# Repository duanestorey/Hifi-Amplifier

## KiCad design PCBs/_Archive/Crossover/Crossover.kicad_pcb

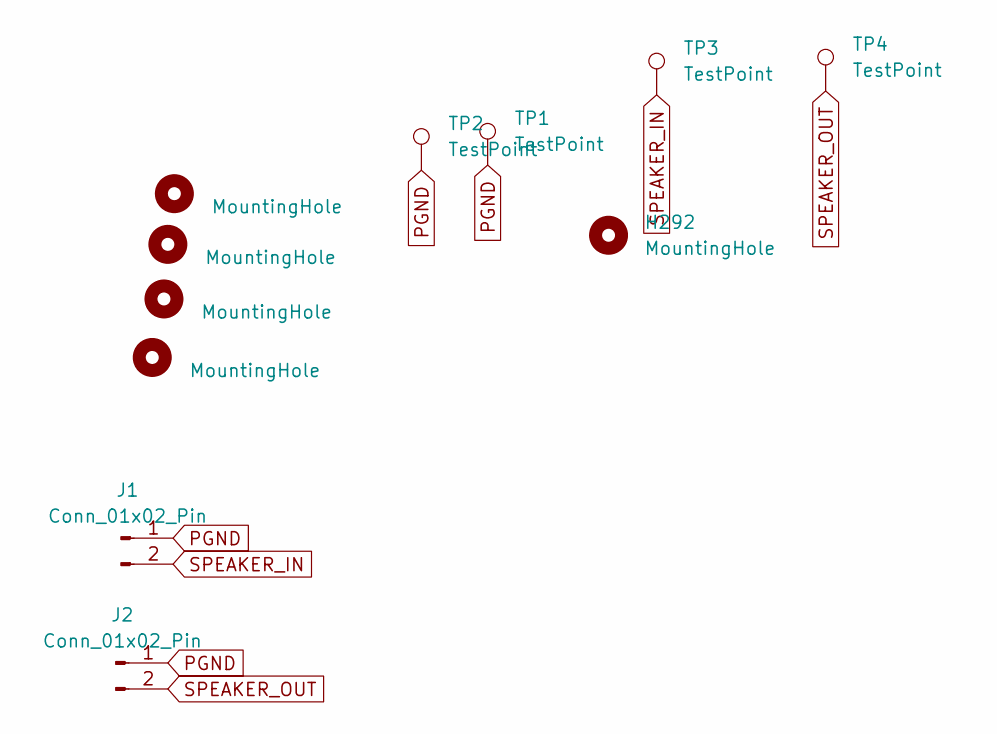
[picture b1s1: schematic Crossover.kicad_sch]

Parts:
H1, H2, H3, H4: MountingHole; MountingHole_3.2mm_M3
H292: MountingHole; MountingHole_2.2mm_M2
J1, J2: Conn_01x02_Pin; JST_VH_B2P-VH_1x02_P3.96mm_Vertical
TP1, TP2, TP3, TP4: TestPoint; TestPoint_Loop_D2.50mm_Drill1.85mm

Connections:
PGND: J1.1, J2.1, TP1.1, TP2.1
SPEAKER_IN: J1.2, TP3.1
SPEAKER_OUT: J2.2, TP4.1

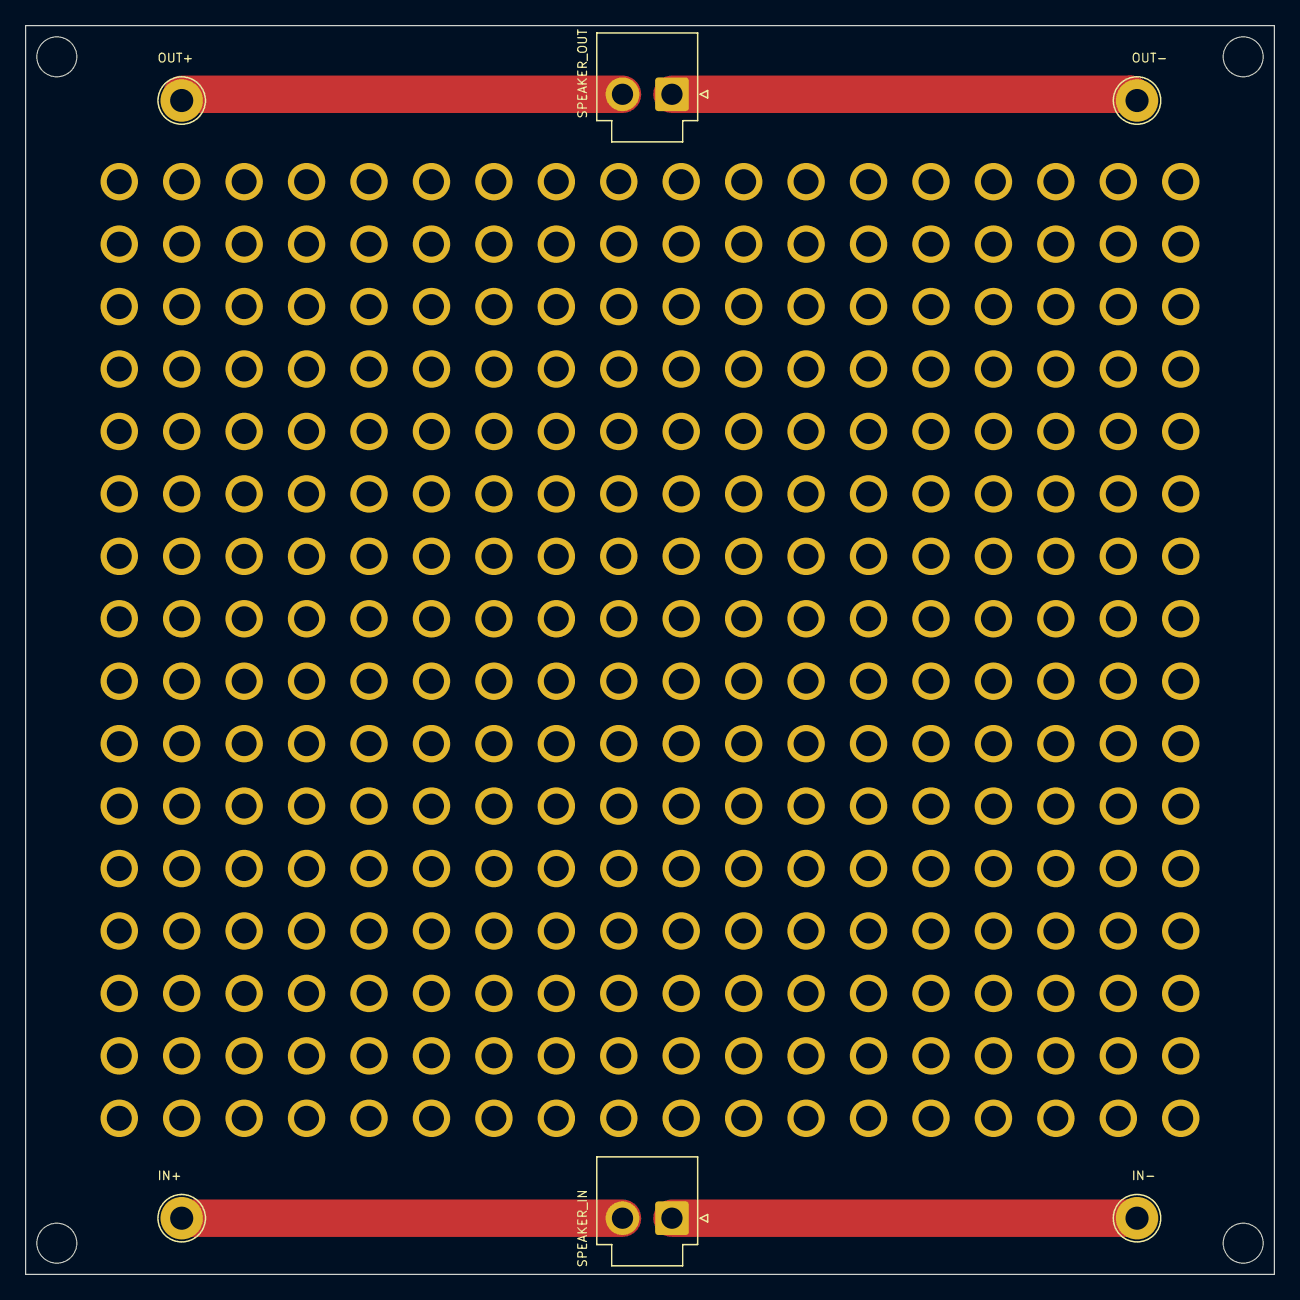
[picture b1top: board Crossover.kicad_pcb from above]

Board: 2 copper layers, 100.0 x 100.0 mm, 298 parts (0 on the bottom side), 3 nets.

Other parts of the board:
H5, H6, H7, H8, H9, H10, H11, H12, H13, H14, H15, H16, H17, H18, H19, H20, H21, H22, H23, H24, H25, H26, H27, H28, H29, H30, H31, H32, H33, H34, H35, H36, H37, H38, H39, H40, H41, H42, H43, H44, H45, H46, H47, H48, H49, H50, H51, H52, H53, H54, H55, H56, H57, H58, H59, H60, H61, H62, H63, H64, H65, H66, H67, H68, H69, H70, H71, H72, H73, H74, H75, H76, H77, H78, H79, H80, H81, H82, H83, H84, H85, H86, H87, H88, H89, H90, H91, H92, H93, H94, H95, H96, H97, H98, H99, H100, H101, H102, H103, H104, H105, H106, H107, H108, H109, H110, H111, H112, H113, H114, H115, H116, H117, H118, H119, H120, H121, H122, H123, H124, H125, H126, H127, H128, H129, H130, H131, H132, H133, H134, H135, H136, H137, H138, H139, H140, H141, H142, H143, H144, H145, H146, H147, H148, H149, H150, H151, H152, H153, H154, H155, H156, H157, H158, H159, H160, H161, H162, H163, H164, H165, H166, H167, H168, H169, H170, H171, H172, H173, H174, H175, H176, H177, H178, H179, H180, H181, H182, H183, H184, H185, H186, H187, H188, H189, H190, H191, H192, H193, H194, H195, H196, H197, H198, H199, H200, H201, H202, H203, H204, H205, H206, H207, H208, H209, H210, H211, H212, H213, H214, H215, H216, H217, H218, H219, H220, H221, H222, H223, H224, H225, H226, H227, H228, H229, H230, H231, H232, H233, H234, H235, H236, H237, H238, H239, H240, H241, H242, H243, H244, H245, H246, H247, H248, H249, H250, H251, H252, H253, H254, H255, H256, H257, H258, H259, H260, H261, H262, H263, H264, H265, H266, H267, H268, H269, H270, H271, H272, H273, H274, H275, H276, H277, H278, H279, H280, H281, H282, H283, H284, H285, H286, H287, H288, H289, H290, H291: MountingHole; MountingHole_2.2mm_M2

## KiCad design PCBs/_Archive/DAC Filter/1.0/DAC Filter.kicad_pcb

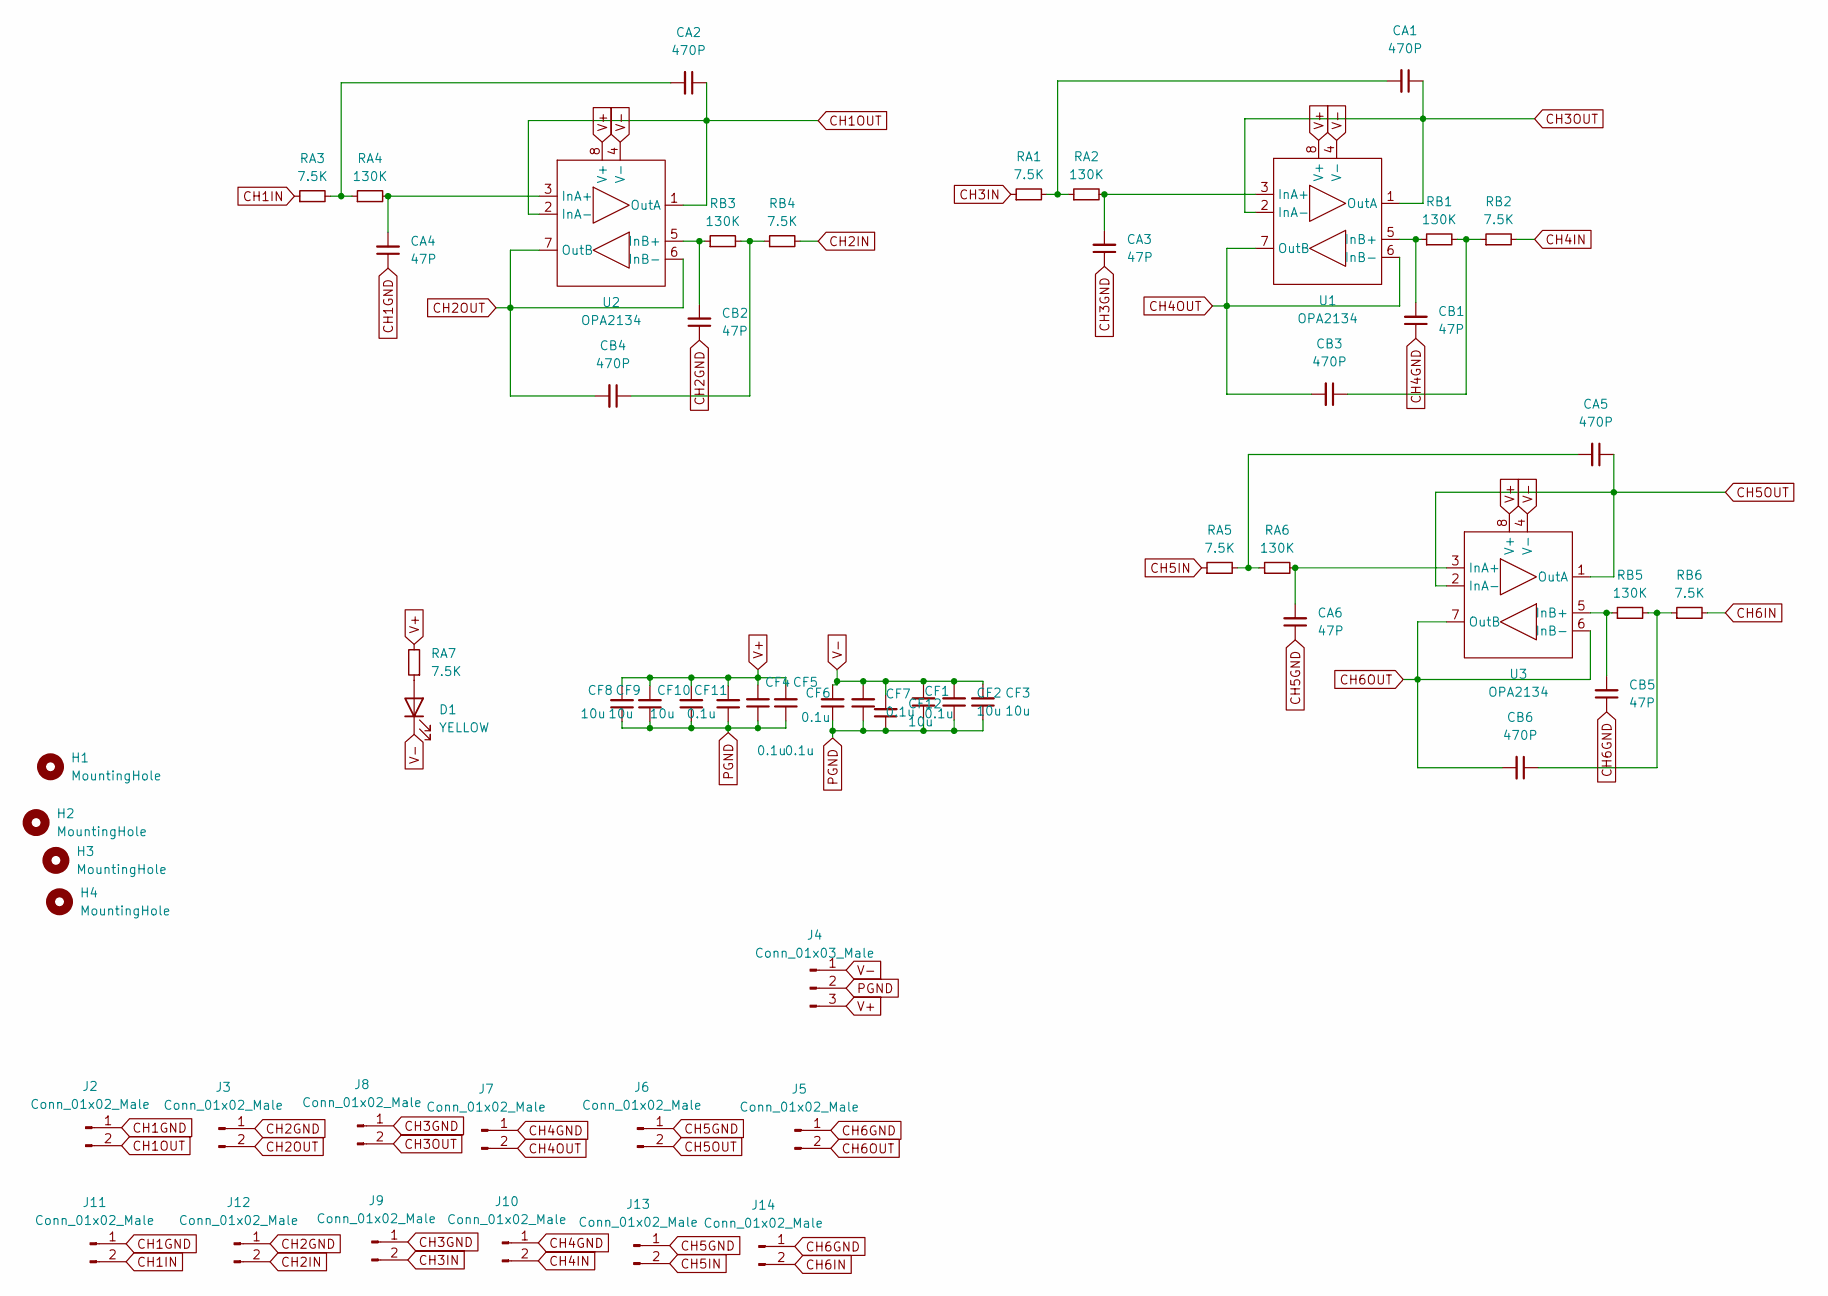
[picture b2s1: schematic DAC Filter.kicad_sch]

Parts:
CA1, CA2, CA5: 470P; C_1206_3216Metric_Pad1.33x1.80mm_HandSolder
CA3, CA4, CA6: 47P; C_1206_3216Metric_Pad1.33x1.80mm_HandSolder
CB1, CB2, CB5: 47P; C_1206_3216Metric_Pad1.33x1.80mm_HandSolder
CB3, CB4, CB6: 470P; C_1206_3216Metric_Pad1.33x1.80mm_HandSolder
CF1, CF4, CF5, CF6, CF7, CF11: 0.1u; C_0805_2012Metric_Pad1.18x1.45mm_HandSolder
CF2, CF3, CF8, CF9, CF10, CF12: 10u; C_1206_3216Metric_Pad1.33x1.80mm_HandSolder
D1: YELLOW; LED_0805_2012Metric_Pad1.15x1.40mm_HandSolder
H1, H2, H3, H4: MountingHole; MountingHole_3.2mm_M3
J2, J3, J5, J6, J7, J8, J9, J10, J11, J12, J13, J14: Conn_01x02_Male; JST_PH_B2B-PH-K_1x02_P2.00mm_Vertical
J4: Conn_01x03_Male; JST_PH_B3B-PH-K_1x03_P2.00mm_Vertical
RA1, RA3, RA5: 7.5K; R_1206_3216Metric_Pad1.30x1.75mm_HandSolder
RA2, RA4, RA6: 130K; R_1206_3216Metric_Pad1.30x1.75mm_HandSolder
RA7: 7.5K; R_0603_1608Metric
RB1, RB3, RB5: 130K; R_1206_3216Metric_Pad1.30x1.75mm_HandSolder
RB2, RB4, RB6: 7.5K; R_1206_3216Metric_Pad1.30x1.75mm_HandSolder
U1, U2, U3: OPA2134; DIP-8_W7.62mm_Socket

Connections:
CH1GND: CA4.1, J2.1, J11.1
CH1IN: J11.2, RA3.1
CH1OUT: CA2.1, J2.2, U2.1 (OutA), U2.2 (InA-)
CH2GND: CB2.1, J3.1, J12.1
CH2IN: J12.2, RB4.2
CH2OUT: CB4.2, J3.2, U2.6 (InB-), U2.7 (OutB)
CH3GND: CA3.1, J8.1, J9.1
CH3IN: J9.2, RA1.1
CH3OUT: CA1.1, J8.2, U1.1 (OutA), U1.2 (InA-)
CH4GND: CB1.1, J7.1, J10.1
CH4IN: J10.2, RB2.2
CH4OUT: CB3.2, J7.2, U1.6 (InB-), U1.7 (OutB)
CH5GND: CA6.1, J6.1, J13.1
CH5IN: J13.2, RA5.1
CH5OUT: CA5.1, J6.2, U3.1 (OutA), U3.2 (InA-)
CH6GND: CB5.1, J5.1, J14.1
CH6IN: J14.2, RB6.2
CH6OUT: CB6.2, J5.2, U3.6 (InB-), U3.7 (OutB)
unnamed: CA1.2, RA1.2, RA2.1
unnamed: CA2.2, RA3.2, RA4.1
unnamed: CA5.2, RA5.2, RA6.1
unnamed: CB3.1, RB1.2, RB2.1
unnamed: CB4.1, RB3.2, RB4.1
unnamed: CB6.1, RB5.2, RB6.1
unnamed: D1.2 (A), RA7.1
unnamed: CA3.2, RA2.2, U1.3 (InA+)
unnamed: CB1.2, RB1.1, U1.5 (InB+)
unnamed: CA4.2, RA4.2, U2.3 (InA+)
unnamed: CB2.2, RB3.1, U2.5 (InB+)
unnamed: CA6.2, RA6.2, U3.3 (InA+)
unnamed: CB5.2, RB5.1, U3.5 (InB+)
PGND: CF1.1, CF2.1, CF3.1, CF4.1, CF5.1, CF6.1, CF7.1, CF8.1, CF9.1, CF10.1, CF11.1, CF12.1, J4.2
V+: CF4.2, CF5.2, CF8.2, CF9.2, CF10.2, CF11.2, J4.3, RA7.2, U1.8 (V+), U2.8 (V+), U3.8 (V+)
V-: CF1.2, CF2.2, CF3.2, CF6.2, CF7.2, CF12.2, D1.1 (K), J4.1, U1.4 (V-), U2.4 (V-), U3.4 (V-)

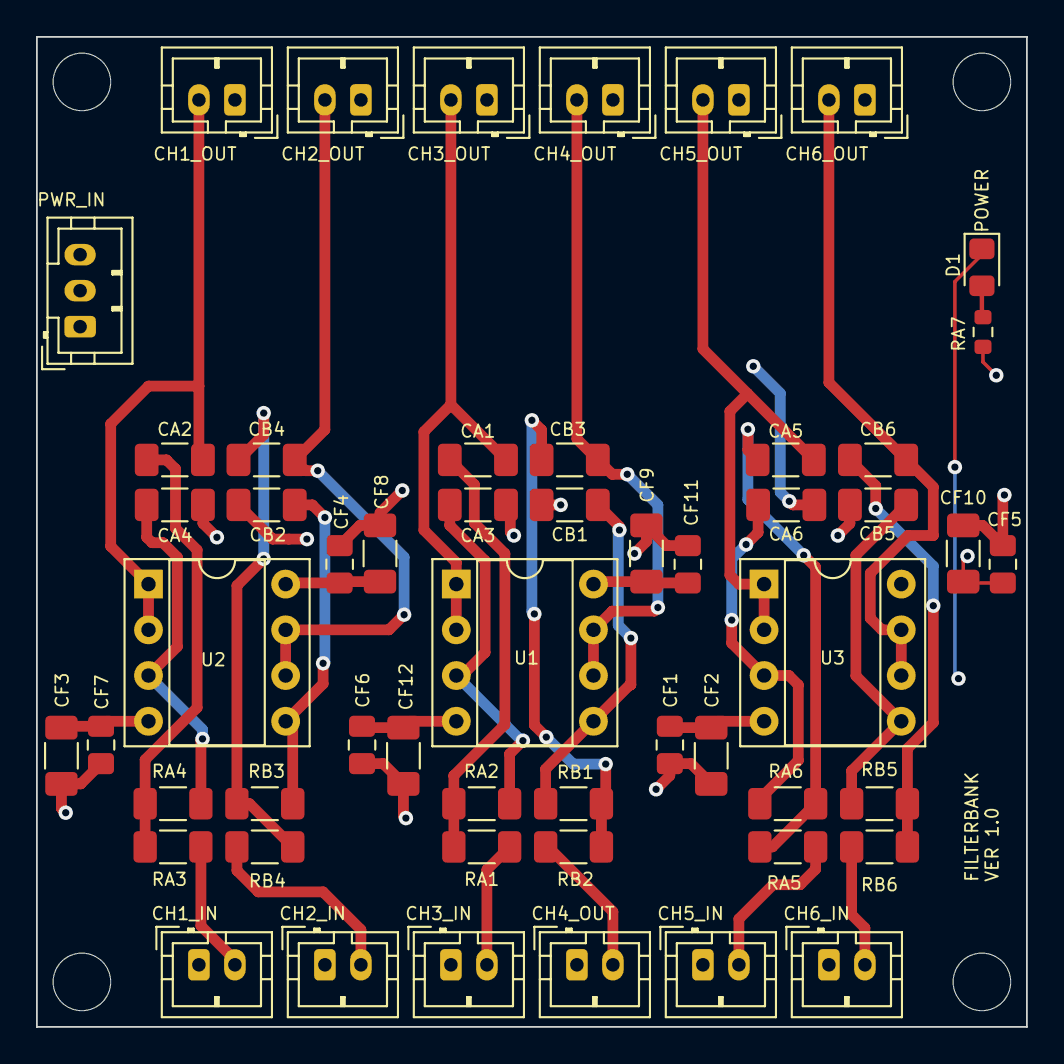
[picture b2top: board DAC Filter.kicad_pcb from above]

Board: 4 copper layers, 55.0 x 55.0 mm, 58 parts (0 on the bottom side), 34 nets.

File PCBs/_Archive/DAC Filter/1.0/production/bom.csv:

Designator,Footprint,Quantity,Value,LCSC Part #
"CA1, CA2, CA5, CB3, CB4, CB6",C_1206_3216Metric_Pad1.33x1.80mm_HandSolder,6,470P,
"CA3, CA4, CA6, CB1, CB2, CB5",C_1206_3216Metric_Pad1.33x1.80mm_HandSolder,6,47P,
"CF1, CF11, CF4, CF5, CF6, CF7",C_0805_2012Metric_Pad1.18x1.45mm_HandSolder,6,0.1u,
"CF10, CF12, CF2, CF3, CF8, CF9",C_1206_3216Metric_Pad1.33x1.80mm_HandSolder,6,10u,
D1,LED_0805_2012Metric_Pad1.15x1.40mm_HandSolder,1,YELLOW,
"H1, H2, H3, H4",MountingHole_3.2mm_M3,4,MountingHole,
"J10, J11, J12, J13, J14, J2, J3, J5, J6, J7, J8, J9",JST_PH_B2B-PH-K_1x02_P2.00mm_Vertical,12,Conn_01x02_Male,
J4,JST_PH_B3B-PH-K_1x03_P2.00mm_Vertical,1,Conn_01x03_Male,
"RA1, RA3, RA5, RB2, RB4, RB6",R_1206_3216Metric_Pad1.30x1.75mm_HandSolder,6,7.5K,
"RA2, RA4, RA6, RB1, RB3, RB5",R_1206_3216Metric_Pad1.30x1.75mm_HandSolder,6,130K,
RA7,R_0603_1608Metric,1,7.5K,
"U1, U2, U3",DIP-8_W7.62mm_Socket,3,OPA2134,

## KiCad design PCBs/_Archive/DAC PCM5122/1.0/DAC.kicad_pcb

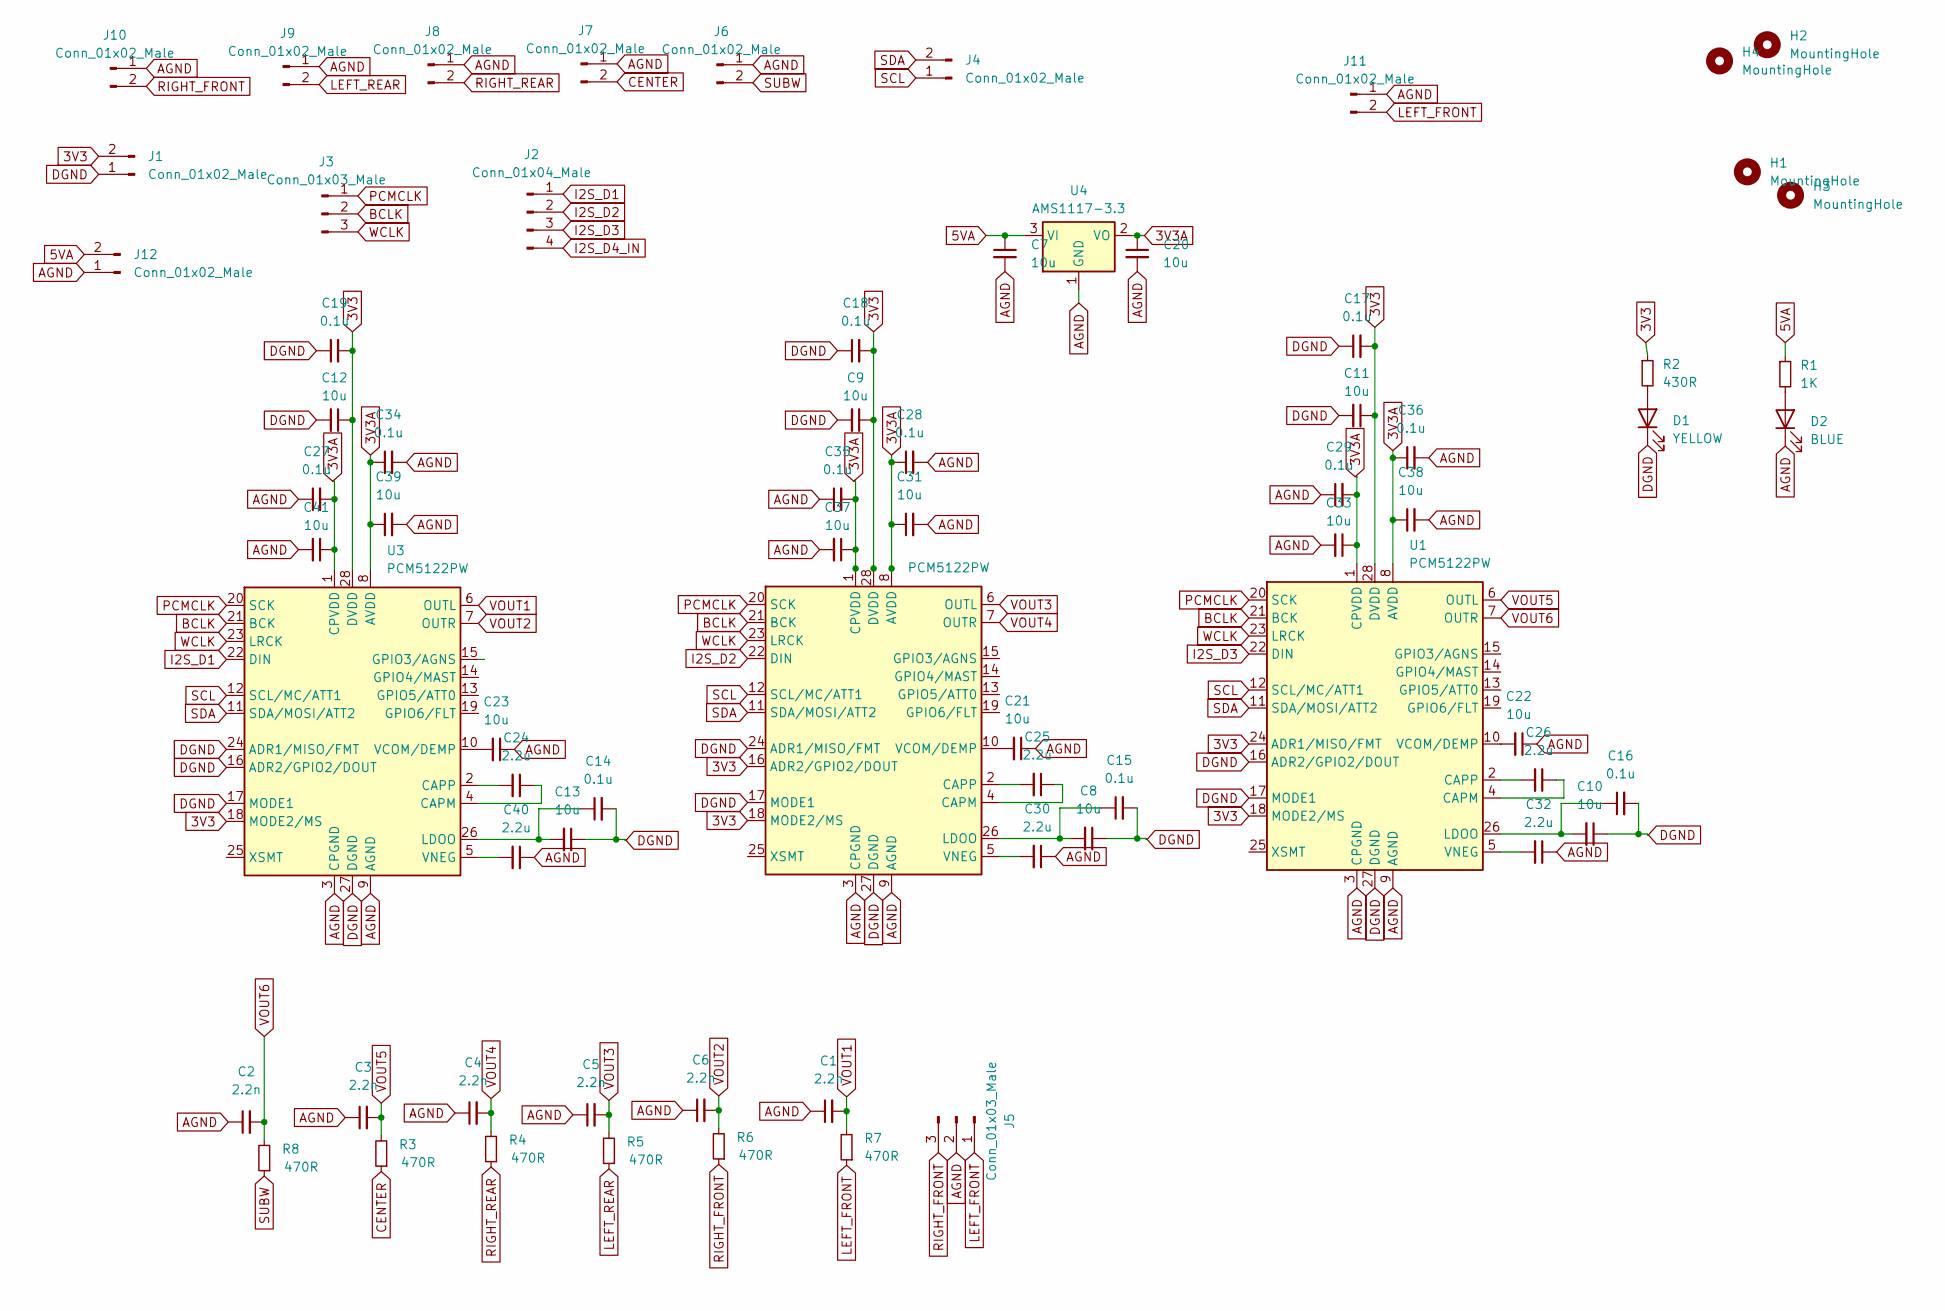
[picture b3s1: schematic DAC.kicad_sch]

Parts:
C1, C2, C3, C4, C5, C6: 2.2n; C_1206_3216Metric_Pad1.33x1.80mm_HandSolder
C7, C8, C9, C10, C11, C12, C13, C20, C21, C22, C23, C31, C33, C37, C38, C39, C41: 10u; C_1206_3216Metric_Pad1.33x1.80mm_HandSolder
C14, C15, C16, C17, C18, C19, C27, C28, C29, C34, C35, C36: 0.1u; C_0805_2012Metric_Pad1.18x1.45mm_HandSolder
C24, C25, C26, C30, C32, C40: 2.2u; C_1206_3216Metric_Pad1.33x1.80mm_HandSolder
D1: YELLOW; LED_0805_2012Metric_Pad1.15x1.40mm_HandSolder
D2: BLUE; LED_0805_2012Metric_Pad1.15x1.40mm_HandSolder
H1, H2, H3, H4: MountingHole; MountingHole_3.2mm_M3
J1, J4, J6, J7, J8, J9, J10, J11, J12: Conn_01x02_Male; JST_PH_B2B-PH-K_1x02_P2.00mm_Vertical
J2: Conn_01x04_Male; JST_PH_B4B-PH-K_1x04_P2.00mm_Vertical
J3: Conn_01x03_Male; JST_PH_B3B-PH-K_1x03_P2.00mm_Vertical
J5: Conn_01x03_Male; PinHeader_1x03_P2.54mm_Vertical
R1: 1K; R_0603_1608Metric_Pad0.98x0.95mm_HandSolder
R2: 430R; R_0603_1608Metric_Pad0.98x0.95mm_HandSolder
R3, R4, R5, R6, R7, R8: 470R; R_1206_3216Metric_Pad1.30x1.75mm_HandSolder
U1, U2, U3: PCM5122PW; TSSOP-28_4.4x9.7mm_P0.65mm
U4: AMS1117-3.3; SOT-223-3_TabPin2

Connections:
3V3: C9.1, C11.1, C12.1, C17.2, C18.2, C19.2, J1.2, R2.1, U1.18 (MODE2/MS), U1.24 (ADR1/MISO/FMT), U1.28 (DVDD), U2.16 (ADR2/GPIO2/DOUT), U2.18 (MODE2/MS), U2.28 (DVDD), U3.18 (MODE2/MS), U3.28 (DVDD)
3V3A: C20.1, C27.2, C28.1, C29.2, C31.1, C33.1, C34.1, C35.2, C36.1, C37.1, C38.1, C39.1, C41.1, U1.1 (CPVDD), U1.8 (AVDD), U2.1 (CPVDD), U2.8 (AVDD), U3.1 (CPVDD), U3.8 (AVDD), U4.2 (VO)
5VA: C7.1, J1.4, J12.2, R1.1, U4.3 (VI)
AGND: C1.1, C2.1, C3.1, C4.1, C5.1, C6.1, C7.2, C20.2, C21.1, C22.1, C23.1, C27.1, C28.2, C29.1, C30.1, C31.2, C32.1, C33.2, C34.2, C35.1, C36.2, C37.2, C38.2, C39.2, C40.1, C41.2, D2.1 (K), J1.3, J5.2, J6.1, J7.1, J8.1, J9.1, J10.1, J11.1, J12.1, U1.3 (CPGND), U1.9 (AGND), U2.3 (CPGND), U2.9 (AGND), U3.3 (CPGND), U3.9 (AGND), U4.1 (GND)
BCLK: J3.2, U1.21 (BCK), U2.21 (BCK), U3.21 (BCK)
CENTER: J7.2, R3.1
DGND: C8.1, C9.2, C10.1, C11.2, C12.2, C13.1, C14.2, C15.2, C16.2, C17.1, C18.1, C19.1, D1.1 (K), J1.1, U1.16 (ADR2/GPIO2/DOUT), U1.17 (MODE1), U1.27 (DGND), U2.17 (MODE1), U2.24 (ADR1/MISO/FMT), U2.27 (DGND), U3.16 (ADR2/GPIO2/DOUT), U3.17 (MODE1), U3.24 (ADR1/MISO/FMT), U3.27 (DGND)
I2S_D1: J2.1, U3.22 (DIN)
I2S_D2: J2.2, U2.22 (DIN)
I2S_D3: J2.3, U1.22 (DIN)
I2S_D4_IN: J2.4
LEFT_FRONT: J5.1, J11.2, R7.1
LEFT_REAR: J9.2, R5.1
unnamed: D1.2 (A), R2.2
unnamed: D2.2 (A), R1.2
unnamed: C26.1, U1.4 (CAPM)
unnamed: C26.2, U1.2 (CAPP)
unnamed: C10.2, C16.1, U1.26 (LDOO)
unnamed: C22.2, U1.10 (VCOM/DEMP)
unnamed: C32.2, U1.5 (VNEG)
unnamed: C25.1, U2.4 (CAPM)
unnamed: C25.2, U2.2 (CAPP)
unnamed: C8.2, C15.1, U2.26 (LDOO)
unnamed: C21.2, U2.10 (VCOM/DEMP)
unnamed: C30.2, U2.5 (VNEG)
unnamed: C24.1, U3.4 (CAPM)
unnamed: C24.2, U3.2 (CAPP)
unnamed: C13.2, C14.1, U3.26 (LDOO)
unnamed: C23.2, U3.10 (VCOM/DEMP)
unnamed: C40.2, U3.5 (VNEG)
PCMCLK: J3.1, U1.20 (SCK), U2.20 (SCK), U3.20 (SCK)
RIGHT_FRONT: J5.3, J10.2, R6.1
RIGHT_REAR: J8.2, R4.1
SCL: J4.1, U1.12 (SCL/MC/ATT1), U2.12 (SCL/MC/ATT1), U3.12 (SCL/MC/ATT1)
SDA: J4.2, U1.11 (SDA/MOSI/ATT2), U2.11 (SDA/MOSI/ATT2), U3.11 (SDA/MOSI/ATT2)
SUBW: J6.2, R8.1
VOUT1: C1.2, R7.2, U3.6 (OUTL)
VOUT2: C6.2, R6.2, U3.7 (OUTR)
VOUT3: C5.2, R5.2, U2.6 (OUTL)
VOUT4: C4.2, R4.2, U2.7 (OUTR)
VOUT5: C3.2, R3.2, U1.6 (OUTL)
VOUT6: C2.2, R8.2, U1.7 (OUTR)
WCLK: J3.3, U1.23 (LRCK), U2.23 (LRCK), U3.23 (LRCK)

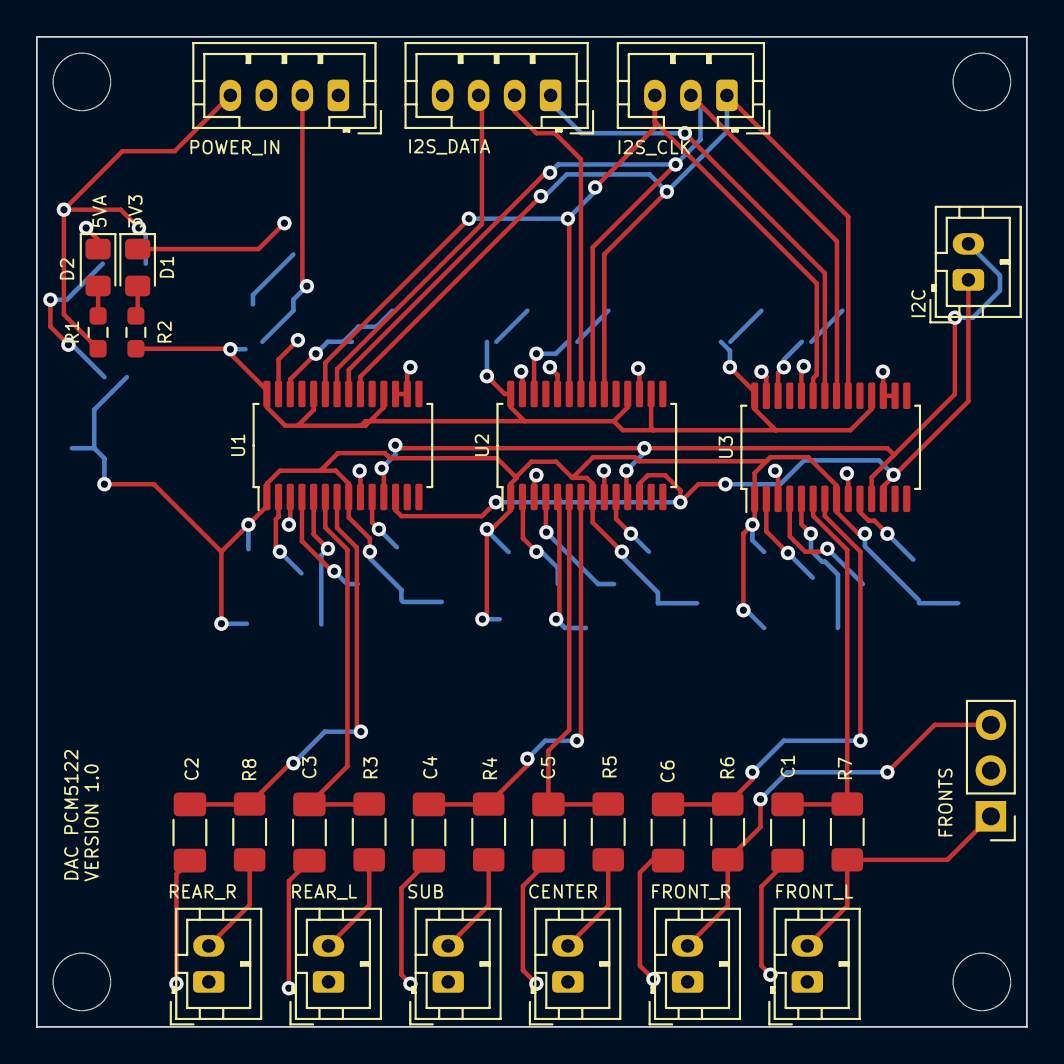
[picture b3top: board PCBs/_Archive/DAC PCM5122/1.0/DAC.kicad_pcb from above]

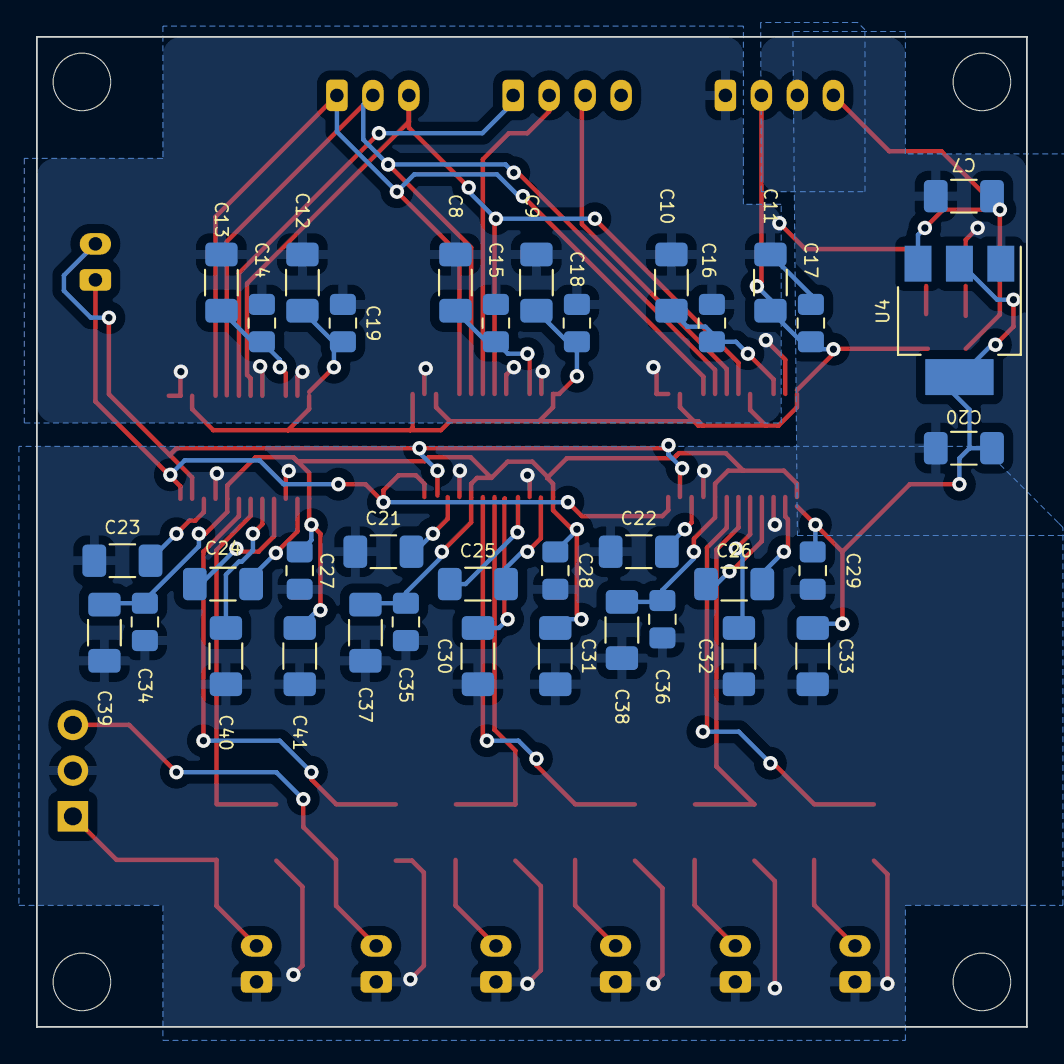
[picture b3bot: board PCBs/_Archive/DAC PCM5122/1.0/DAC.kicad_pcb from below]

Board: 2 copper layers, 55.0 x 55.0 mm, 70 parts (36 on the bottom side), 42 nets.

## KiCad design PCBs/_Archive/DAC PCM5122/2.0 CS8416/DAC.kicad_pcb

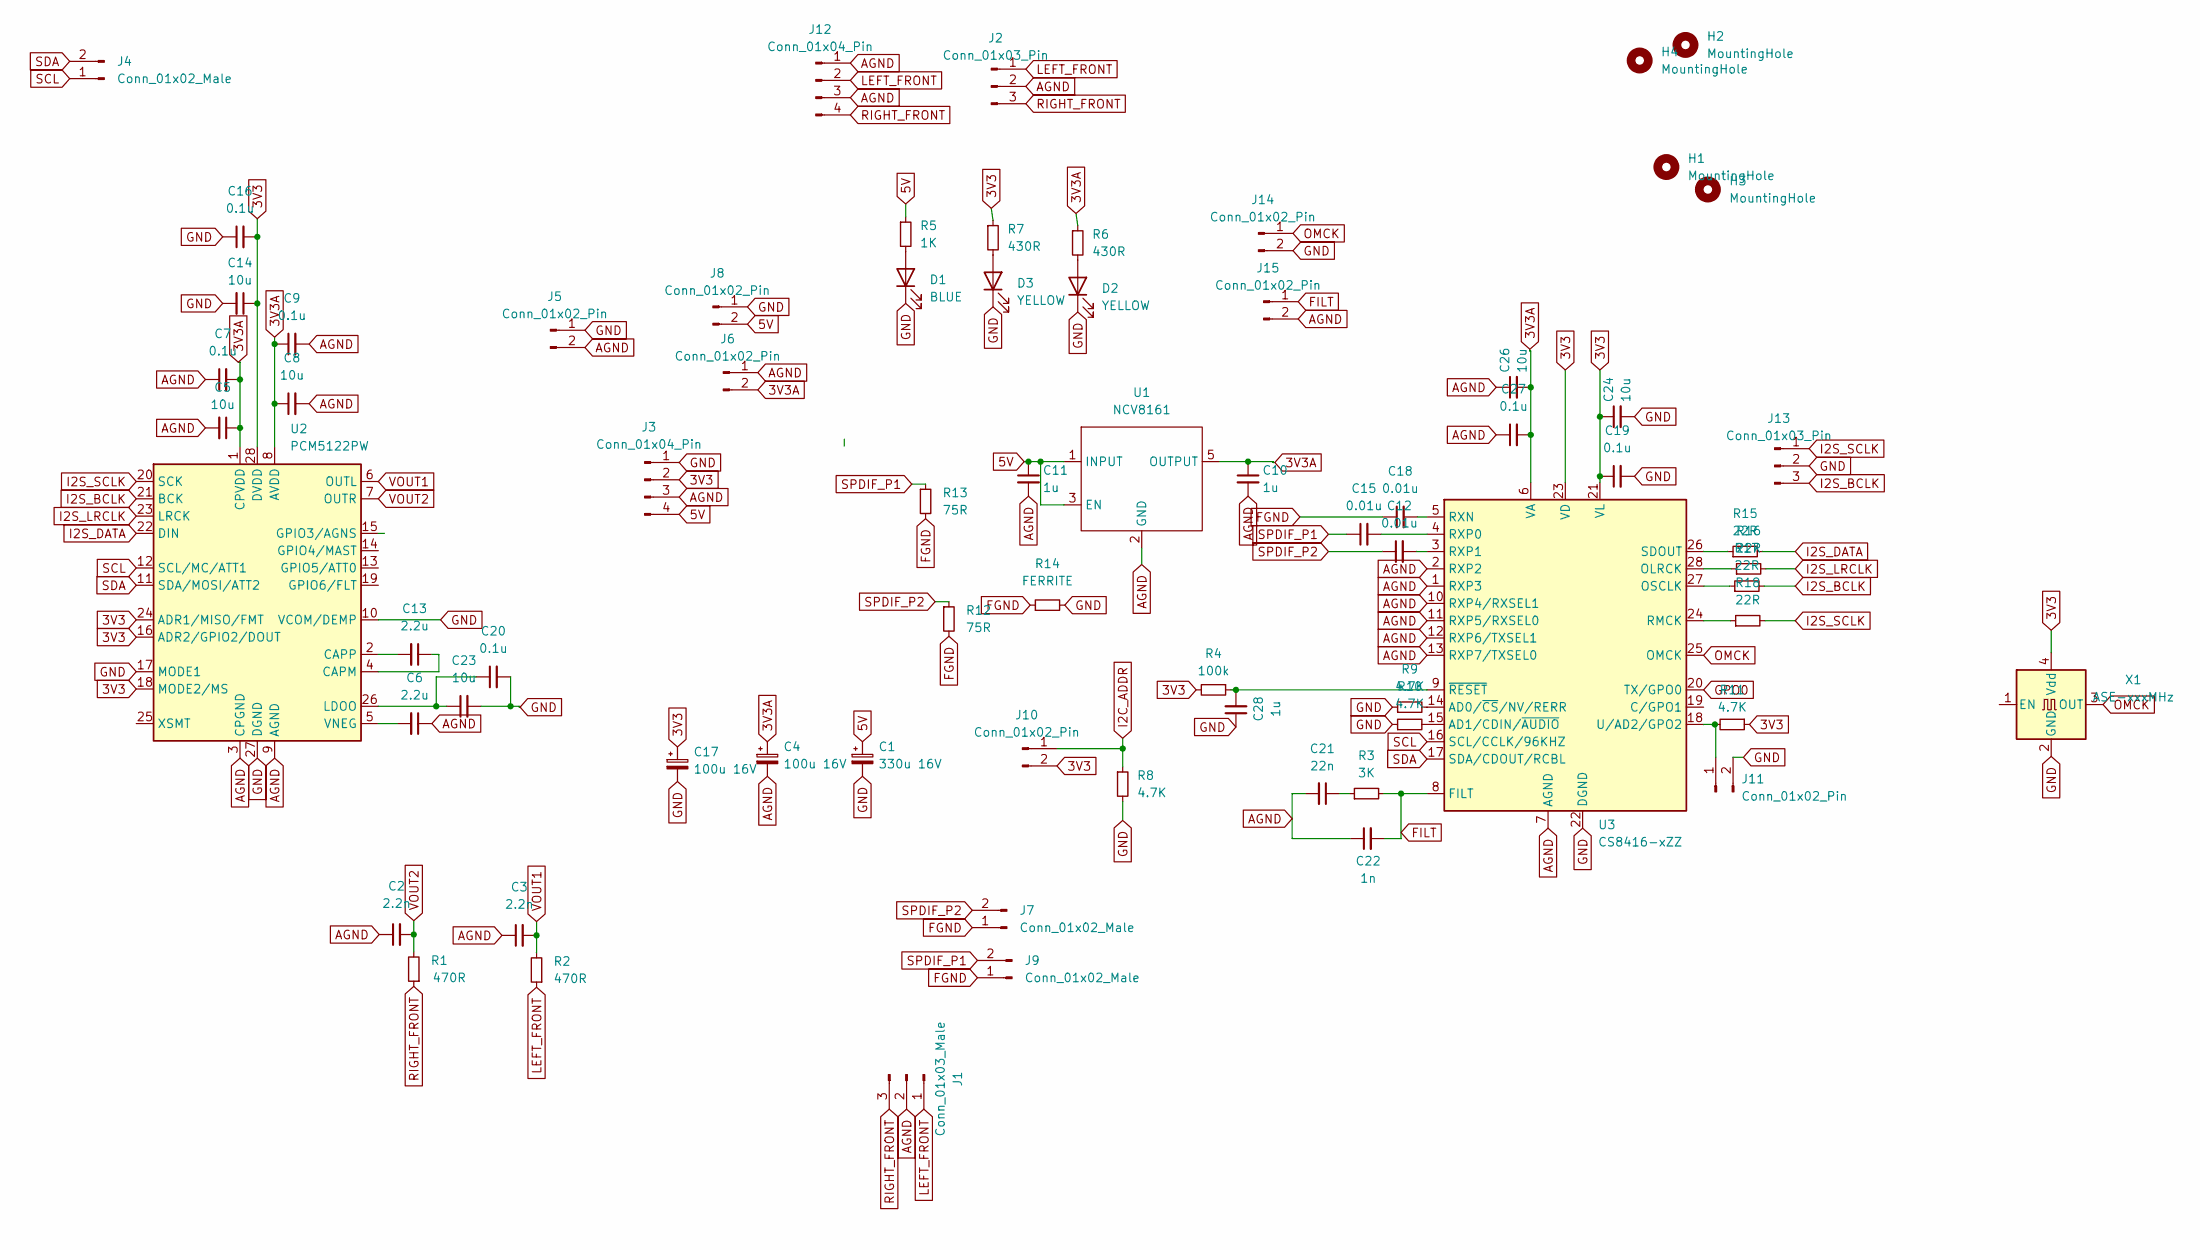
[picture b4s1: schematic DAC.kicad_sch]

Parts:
C1: 330u 16V; CP_Radial_D8.0mm_P2.50mm
C2, C3: 2.2n; C_1206_3216Metric_Pad1.33x1.80mm_HandSolder
C4, C17: 100u 16V; CP_Radial_D5.0mm_P2.50mm
C5, C8, C14, C23, C24, C26: 10u; C_1206_3216Metric_Pad1.33x1.80mm_HandSolder
C6, C13: 2.2u; C_1206_3216Metric_Pad1.33x1.80mm_HandSolder
C7, C9, C16, C19, C20, C27: 0.1u; C_0805_2012Metric_Pad1.18x1.45mm_HandSolder
C10, C11: 1u; C_1206_3216Metric_Pad1.33x1.80mm_HandSolder
C12, C15, C18: 0.01u; C_0805_2012Metric_Pad1.18x1.45mm_HandSolder
C21: 22n; C_0805_2012Metric_Pad1.18x1.45mm_HandSolder
C22: 1n; C_0805_2012Metric_Pad1.18x1.45mm_HandSolder
C28: 1u; C_0805_2012Metric_Pad1.18x1.45mm_HandSolder
D1: BLUE; LED_0805_2012Metric_Pad1.15x1.40mm_HandSolder
D2, D3: YELLOW; LED_0805_2012Metric_Pad1.15x1.40mm_HandSolder
H1, H2, H3, H4: MountingHole; MountingHole_3.2mm_M3
J1: Conn_01x03_Male; PinHeader_1x03_P2.54mm_Vertical
J2: Conn_01x03_Pin; JST_PH_B3B-PH-K_1x03_P2.00mm_Vertical
J3: Conn_01x04_Pin; JST_XH_B4B-XH-A_1x04_P2.50mm_Vertical
J4: Conn_01x02_Male; JST_PH_B2B-PH-K_1x02_P2.00mm_Vertical
J5, J6, J8, J10, J11, J14, J15: Conn_01x02_Pin; PinHeader_1x02_P2.54mm_Vertical
J7, J9: Conn_01x02_Male; JST_XH_B2B-XH-A_1x02_P2.50mm_Vertical
J12: Conn_01x04_Pin; JST_PH_B4B-PH-K_1x04_P2.00mm_Vertical
J13: Conn_01x03_Pin; PinHeader_1x03_P2.54mm_Vertical
R1, R2: 470R; R_1206_3216Metric_Pad1.30x1.75mm_HandSolder
R3: 3K; R_0603_1608Metric_Pad0.98x0.95mm_HandSolder
R4: 100k; R_0603_1608Metric_Pad0.98x0.95mm_HandSolder
R5: 1K; R_0603_1608Metric_Pad0.98x0.95mm_HandSolder
R6, R7: 430R; R_0603_1608Metric_Pad0.98x0.95mm_HandSolder
R8, R9, R10, R11: 4.7K; R_0603_1608Metric_Pad0.98x0.95mm_HandSolder
R12, R13: 75R; R_0603_1608Metric_Pad0.98x0.95mm_HandSolder
R14: FERRITE; R_0603_1608Metric_Pad0.98x0.95mm_HandSolder
R15, R16, R17, R18: 22R; R_0603_1608Metric_Pad0.98x0.95mm_HandSolder
U1: NCV8161; TSOT-23-5
U2: PCM5122PW; TSSOP-28_4.4x9.7mm_P0.65mm
U3: CS8416-xZZ; SOIC-28W_7.5x17.9mm_P1.27mm
X1: ASE-xxxMHz; Oscillator_SMD_Abracon_ASE-4Pin_3.2x2.5mm

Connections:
3V3A: C4.1, C5.1, C7.2, C8.1, C9.1, C10.1, C26.2, C27.2, J6.2, R6.1, U1.5 (OUTPUT), U2.1 (CPVDD), U2.8 (AVDD), U3.6 (VA)
5V: C1.1, C11.1, J3.4, J8.2, R5.1, U1.1 (INPUT), U1.3 (EN)
AGND: C2.1, C3.1, C4.2, C5.2, C6.1, C7.1, C8.2, C9.2, C10.2, C11.2, C21.2, C22.1, C26.1, C27.1, J1.2, J2.2, J3.3, J5.2, J6.1, J12.1, J12.3, J15.2, U1.2 (GND), U2.3 (CPGND), U2.9 (AGND), U3.1 (RXP3), U3.2 (RXP2), U3.7 (AGND), U3.10 (RXP4/RXSEL1), U3.11 (RXP5/RXSEL0), U3.12 (RXP6/TXSEL1), U3.13 (RXP7/TXSEL0)
FGND: C18.1, J7.1, J9.1, R12.2, R13.2, R14.1
FILT: C22.2, J15.1, R3.2, U3.8 (FILT)
GPO0: U3.20 (TX/GPO0)
I2S_BCLK: J13.3, R17.1, R17.2, U2.21 (BCK), U3.27 (OSCLK)
I2S_DATA: R15.1, R15.2, U2.22 (DIN), U3.26 (SDOUT)
I2S_LRCLK: R16.1, R16.2, U2.23 (LRCK), U3.28 (OLRCK)
I2S_SCLK: J13.1, R18.1, R18.2, U2.20 (SCK), U3.24 (RMCK)
LEFT_FRONT: J1.1, J2.1, J12.2, R2.1
unnamed: C21.1, R3.1
unnamed: D1.2 (A), R5.2
unnamed: D2.2 (A), R6.2
unnamed: D3.2 (A), R7.2
unnamed: J11.1, R11.2, U3.18 (U/AD2/GPO2)
unnamed: C13.1, U2.4 (CAPM)
unnamed: C13.2, U2.2 (CAPP)
unnamed: C20.1, C23.1, U2.26 (LDOO)
unnamed: C6.2, U2.5 (VNEG)
unnamed: R9.2, U3.14 (AD0/~CS/NV/RERR)
unnamed: R10.2, U3.15 (AD1/CDIN/~AUDIO)
unnamed: C18.2, U3.5 (RXN)
unnamed: C15.2, U3.4 (RXP0)
unnamed: C12.2, U3.3 (RXP1)
unnamed: C28.2, R4.1, U3.9 (~RESET)
OMCK: J14.1, U3.25 (OMCK), X1.3 (OUT)
RIGHT_FRONT: J1.3, J2.3, J12.4, R1.1
SCL: J4.1, U2.12 (SCL/MC/ATT1), U3.16 (SCL/CCLK/96KHZ)
SDA: J4.2, U2.11 (SDA/MOSI/ATT2), U3.17 (SDA/CDOUT/RCBL)
SPDIF_P1: C15.1, J9.2, R13.1
SPDIF_P2: C12.1, J7.2, R12.1
VOUT1: C3.2, R2.2, U2.6 (OUTL)
VOUT2: C2.2, R1.2, U2.7 (OUTR)

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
